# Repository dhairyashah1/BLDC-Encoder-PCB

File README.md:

# BLDC-Encoder-PCB

This repository contains KiCAD Design Files for Encoder PCB made using AS5600 hall sensor based Encoder Chip for [SRA-VJTI](https://github.com/SRA-VJTI/)'s BLDC Actuator and Quadraped Testing.

## Schematics

## Renders

### Front View

### General View

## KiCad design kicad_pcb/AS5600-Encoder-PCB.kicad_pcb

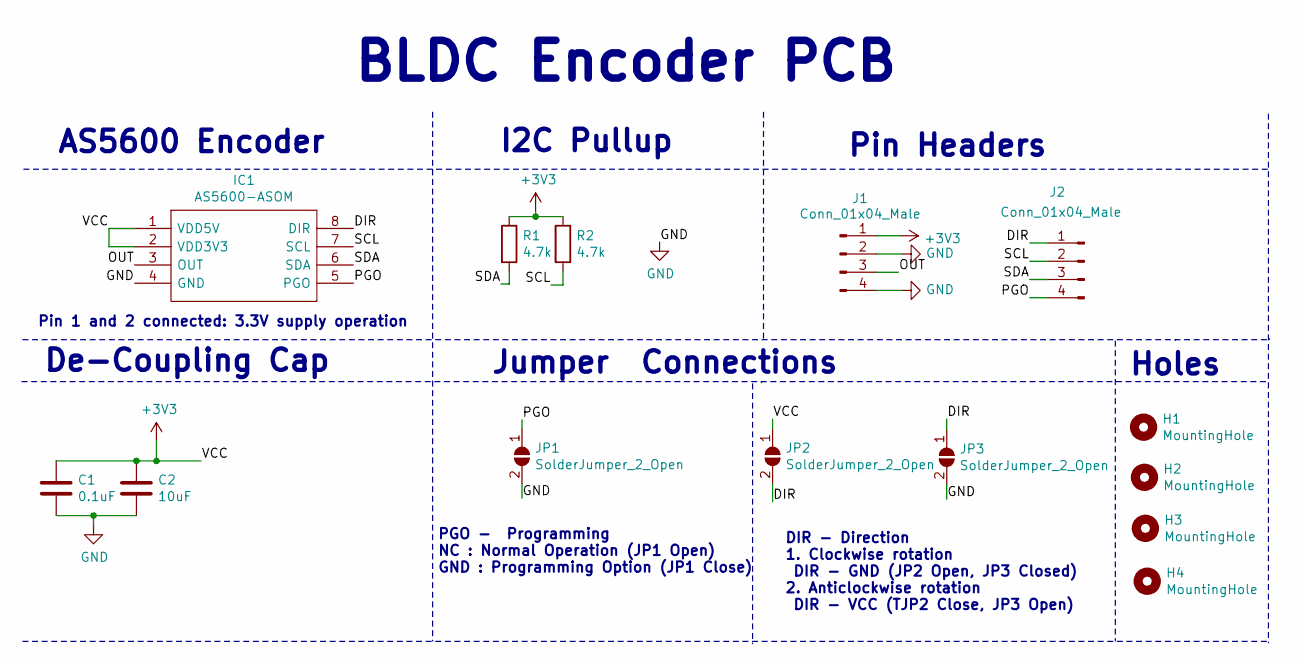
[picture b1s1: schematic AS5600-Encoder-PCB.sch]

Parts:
C1: 0.1uF; C_1206_3216Metric_Pad1.42x1.75mm_HandSolder
C2: 10uF; C_1206_3216Metric_Pad1.42x1.75mm_HandSolder
H1, H2, H3, H4: MountingHole; MountingHole_2.2mm_M2
IC1: AS5600-ASOM; SOIC127P600X175-8N; Manufacturer_Part_Number AS5600-ASOM; Mouser Part Number 985-AS5600-ASOM
J1, J2: Conn_01x04_Male; PinHeader_1x04_P2.54mm_Vertical
JP1, JP2, JP3: SolderJumper_2_Open; SolderJumper-2_P1.3mm_Open_Pad1.0x1.5mm
R1, R2: 4.7k; R_0603_1608Metric_Pad1.05x0.95mm_HandSolder

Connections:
+3V3: C1.2, C2.1, IC1.1 (VDD5V), IC1.2 (VDD3V3), J1.1, JP2.1 (A), R1.1, R2.1
/DIR: IC1.8 (DIR), J2.1, JP2.2 (B), JP3.1 (A)
/OUT: IC1.3 (OUT), J1.3
/PGO: IC1.5 (PGO), J2.4, JP1.1 (A)
/SCL: IC1.7 (SCL), J2.2, R2.2
/SDA: IC1.6 (SDA), J2.3, R1.2
GND: C1.1, C2.2, IC1.4 (GND), J1.2, J1.4, JP1.2 (B), JP3.2 (B)

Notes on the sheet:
I2C Pullup
Pin Headers
De-Coupling Cap
Jumper Connections
PGO - Programming NC : Normal Operation (JP1 Open) GND : Programming Option (JP1 Close)
Pin 1 and 2 connected: 3.3V supply operation
DIR - Direction 1. Clockwise rotation DIR - GND (JP2 Open, JP3 Closed) 2. Anticlockwise rotation DIR - VCC (TJP2 Close, JP3 Open)
AS5600 Encoder
Holes
BLDC Encoder PCB

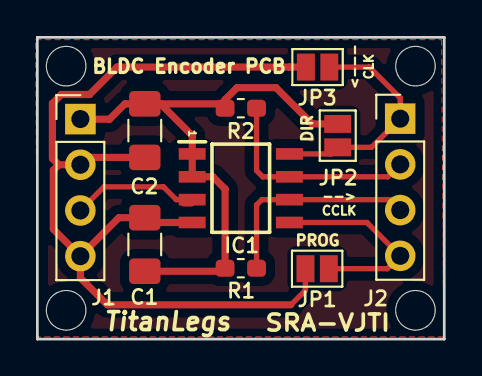
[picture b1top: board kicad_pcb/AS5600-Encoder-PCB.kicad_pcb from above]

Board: 2 copper layers, 22.6 x 16.8 mm, 14 parts (0 on the bottom side), 7 nets.

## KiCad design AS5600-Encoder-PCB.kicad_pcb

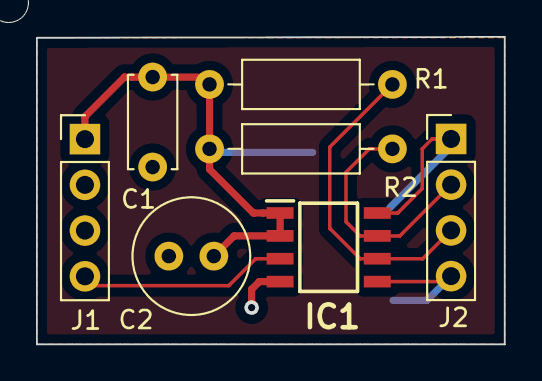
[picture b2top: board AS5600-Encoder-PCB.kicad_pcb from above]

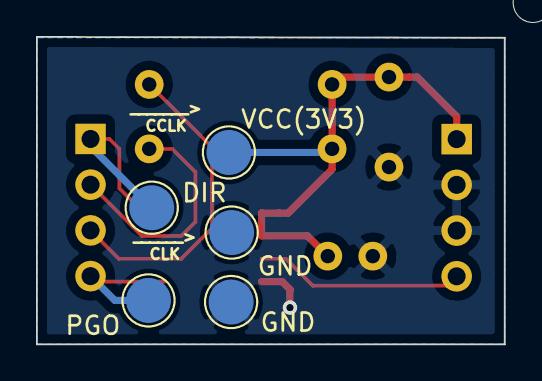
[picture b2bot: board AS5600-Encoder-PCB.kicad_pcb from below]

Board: 2 copper layers, 26.0 x 17.1 mm, 12 parts (5 on the bottom side), 7 nets.

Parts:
C1: 0.1uF; C_Disc_D5.0mm_W2.5mm_P5.00mm
C2: 10uF; C_Radial_D6.3mm_H11.0mm_P2.50mm
DIR: TestPoint; TestPoint_Pad_D2.5mm
GND: TestPoint; TestPoint_Pad_D2.5mm
GND#2: TestPoint; TestPoint_Pad_D2.5mm
IC1: AS5600-ASOM; SOIC127P600X175-8N
J1, J2: Conn_01x04_Male; PinHeader_1x04_P2.54mm_Vertical
PGO: TestPoint; TestPoint_Pad_D2.5mm
R1, R2: 4.7k; R_Axial_DIN0207_L6.3mm_D2.5mm_P10.16mm_Horizontal
VCC(3V3): TestPoint; TestPoint_Pad_D2.5mm

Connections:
+3V3: C1.2, C2.1, IC1.1, IC1.2, J1.1, R1.1, R2.1, VCC(3V3).1
/DIR: DIR.1, IC1.8, J2.1
/OUT: IC1.3, J1.4
/PGO: IC1.5, J2.4, PGO.1
/SCL: IC1.7, J2.2, R2.2
/SDA: IC1.6, J2.3, R1.2
GND: C1.1, C2.2, GND.1, GND#2.1, IC1.4, J1.2, J1.3

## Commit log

2021-08-23 Added PTH PCB for AS5600 Encoder Controller
2021-08-23 Fixed .gitignore
2021-08-24 Restructured file structure
2021-08-24 Restructured libraries
2021-08-24 Added SMD PCB for AS5600 Controller Board
2021-08-24 Added SMD PCB assets
2021-08-24 Added holes, gerbers - SMD PCB
2021-08-24 Added Schematic asset
2021-08-24 Made suggested changes
2021-08-25 Modified and optimized design for 1 layer
2021-08-26 Modified gerbers
2022-02-08 Added PCB layout dimensions
